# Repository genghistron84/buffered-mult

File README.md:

# Buffered Multiple

Minimalist footprint buffered multiple PCB - takes one input and provides 4 buffered outputs.

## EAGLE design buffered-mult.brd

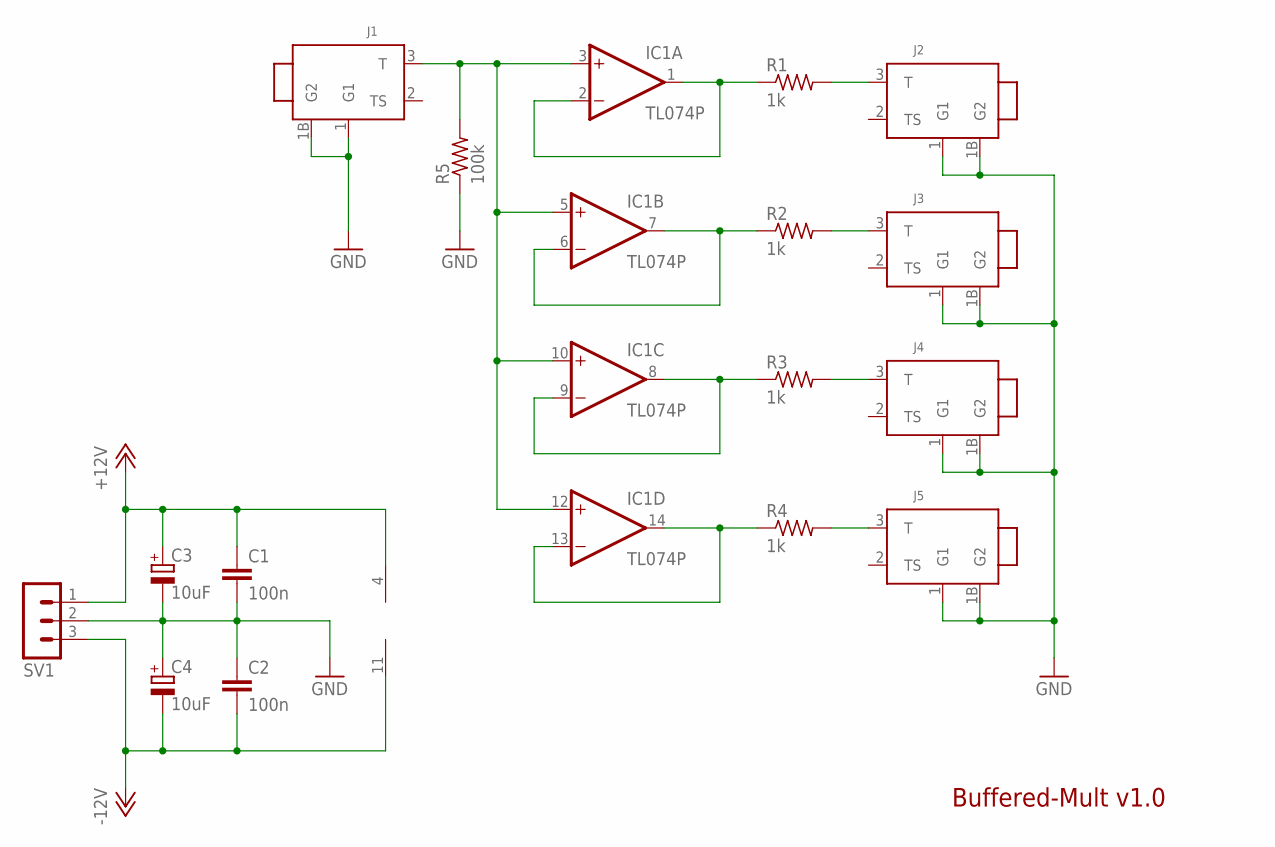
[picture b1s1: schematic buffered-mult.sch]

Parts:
C1, C2: 100n; C025-025X050
C3, C4: 10uF; E2,5-6E
IC1: TL074P; DIL14
J1, J2, J3, J4, J5: THONK_JACK; THONK_JACK_P
R1, R2, R3, R4: 1k; 0207/10
R5: 100k; 0207/10
SV1: MA03-1

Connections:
+12V: C1.1, C3.+, IC1.4 (V+), SV1.1
-12V: C2.2, C4.-, IC1.11 (V-), SV1.3
GND: C1.2, C2.1, C3.-, C4.+, J1.1 (G1), J1.1B (G2), J2.1 (G1), J2.1B (G2), J3.1 (G1), J3.1B (G2), J4.1 (G1), J4.1B (G2), J5.1 (G1), J5.1B (G2), R5.1, SV1.2
unnamed: IC1.1 (OUT), IC1.2 (-IN), R1.1
unnamed: IC1.6 (-IN), IC1.7 (OUT), R2.1
unnamed: IC1.8 (OUT), IC1.9 (-IN), R3.1
unnamed: IC1.13 (-IN), IC1.14 (OUT), R4.1
unnamed: J2.3 (T), R1.2
unnamed: J3.3 (T), R2.2
unnamed: IC1.3 (+IN), IC1.5 (+IN), IC1.10 (+IN), IC1.12 (+IN), J1.3 (T), R5.2
unnamed: J4.3 (T), R3.2
unnamed: J5.3 (T), R4.2

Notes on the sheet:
Buffered-Mult v1.0

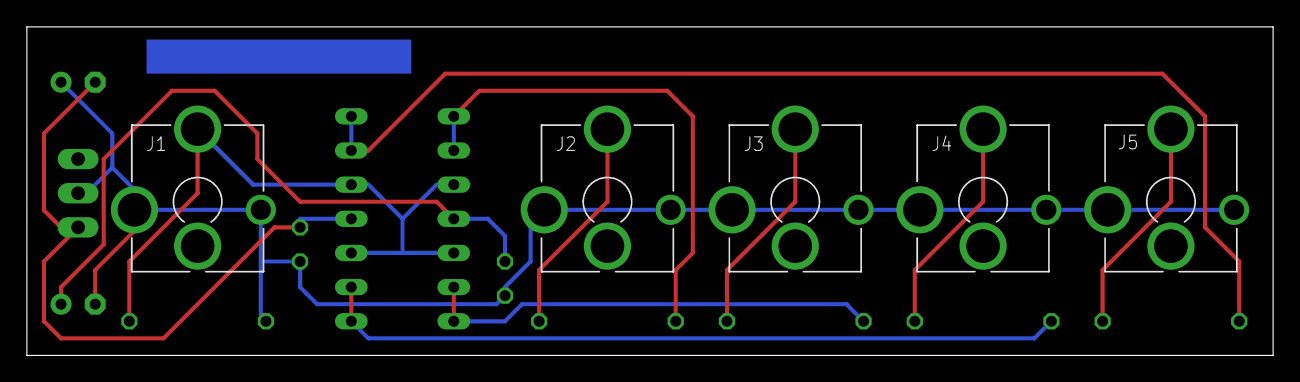
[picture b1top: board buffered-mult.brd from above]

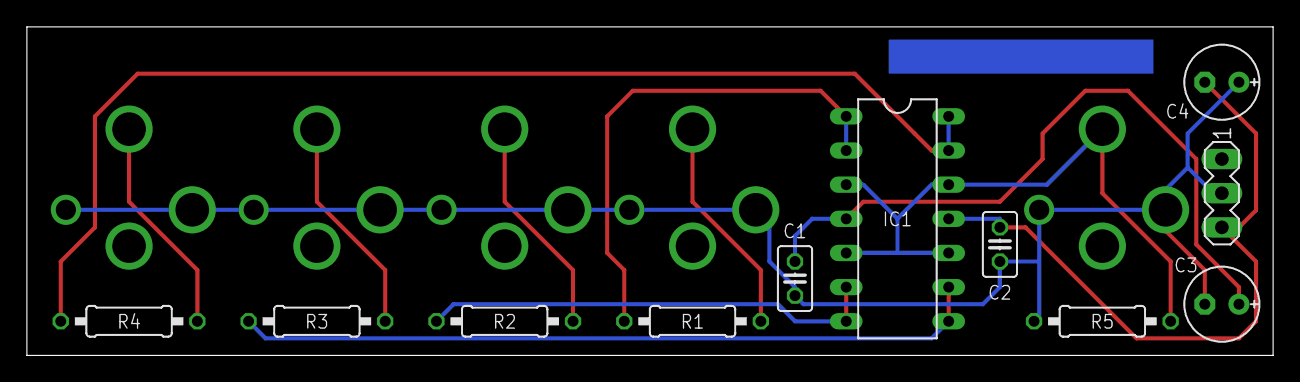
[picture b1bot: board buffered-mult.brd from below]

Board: 2 copper layers, 92.7 x 24.4 mm, 16 parts (11 on the bottom side), 12 nets.

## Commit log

2021-10-24 Add files via upload
    Initial commit
2021-10-24 Add schematic
2021-10-24 Update README.md
    Update readme
